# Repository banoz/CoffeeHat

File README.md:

# CoffeeHat

Basic espresso machine controls on Arduino Nano extension board.

Supports 3-Way valve control, PSM control for a vibe pump based on zero-crossing detector, Qwiic I2C connector for various peripherals (e.g. displays, thermal sensors), full header breakout for Nano pins.

# DISCLAIMER

This project is provided AS-IS, use at your sole discretion and your own risk. Parts of this project can work under dangerous voltages and require special care. Please don't do anything you're not sure about. The maintainer(s) can not be held liable for any suffer or loss or harm or anything else.

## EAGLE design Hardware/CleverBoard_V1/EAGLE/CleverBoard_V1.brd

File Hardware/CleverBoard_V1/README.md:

# Clever board

ESP32-C6 based controller board v1 - WIP

```
J10, J11 - AC input
J12 - pump
J13 - 3-way valve

J1 - UART0 (IO16/IO17)
J2 - I2C (IO6/IO7)
J3 - IO8, IO9
J5 - IO3
J6 - Pressure sensor (IO2, 10K/20K voltage divider)
J7 - Brew (IO22) / Steam (IO23) switch
J8 - IO19, IO20, IO21
J9 - 5V SSR control (IO10 -> SSR1, IO11 -> SSR2)

AC zero-cross sense on IO0
Pump control on IO18
3-Way valve control on IO15

I2C port on IO7(I2C1_SCL)/IO6(I2C1_SDA)
```

Top|Bottom
---|---
|

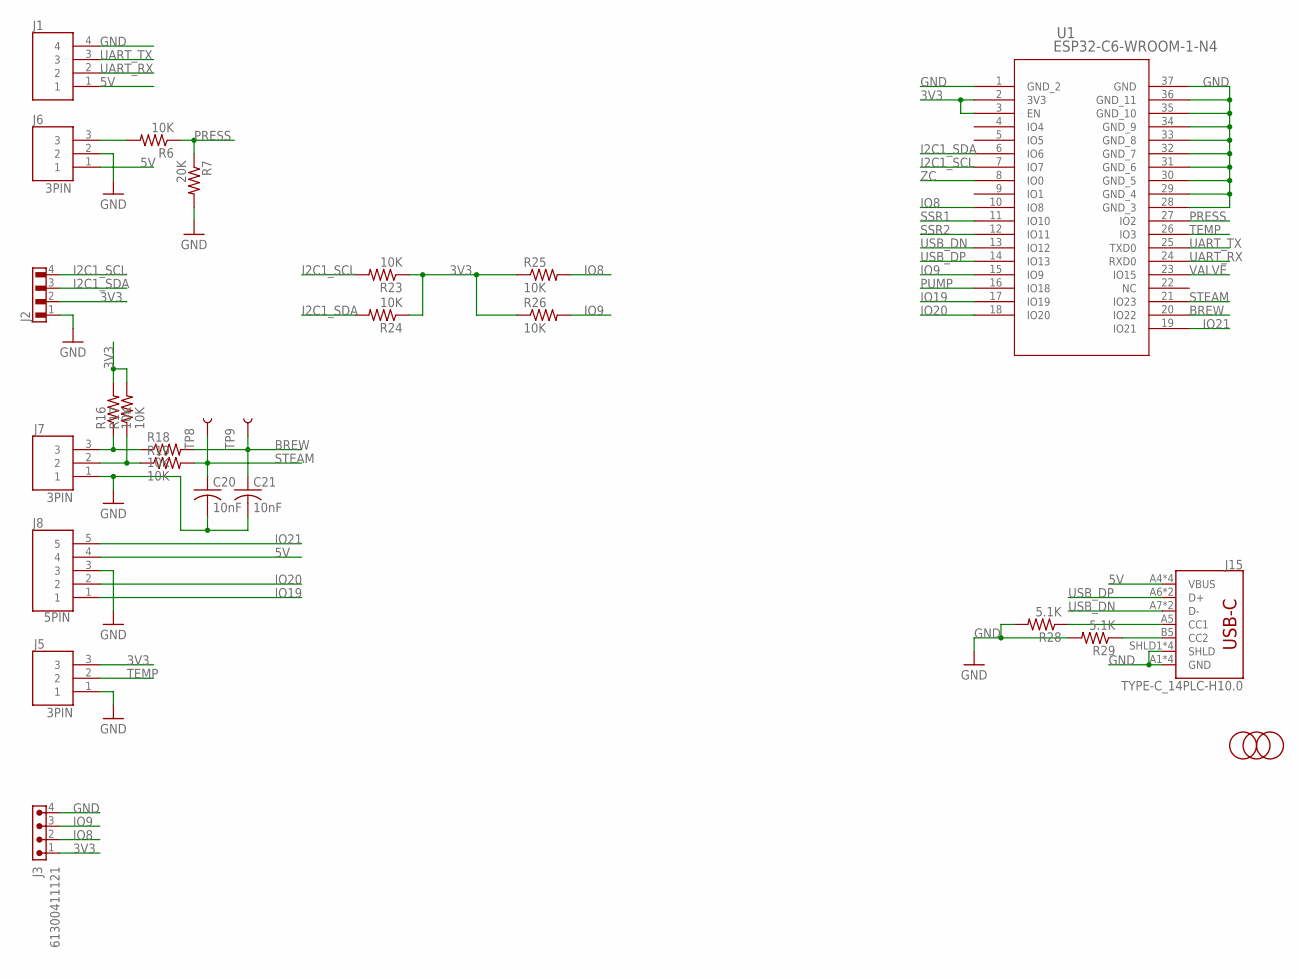
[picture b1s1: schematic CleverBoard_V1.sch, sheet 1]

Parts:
C20, C21: 10nF; C0603; LCSC C100042
J1: 4PIN; B4B-PH-K-S; LCSC C131334
J2: 665104131822; LCSC C160390
J3: 61300411121; LCSC C2691448
J5, J6, J7: 3PIN; B3B-PH-K-S; LCSC C131339
J8: 5PIN; B5B-PH-K-S; LCSC C157993
J15: TYPE-C_14PLC-H10.0; LCSC C3151746
MARK1, MARK2, MARK5: FIDUCIAL; FIDUCIAL_1MM
R6, R16, R17, R18, R19, R23, R24, R25, R26: 10K; R0603; LCSC C98220
R7: 20K; R0603; LCSC C105575
R28, R29: 5.1K; R0603; LCSC C105580
TP8, TP9: TEST-POINT3; PAD.03X.03
U1: ESP32-C6-WROOM-1-N4; MOD28_ESP32-C6-WROOM-1_EXP; LCSC C5366877

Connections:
3V3: J2.2, J3.1, J5.3, R16.2, R17.2, R23.1, R24.1, R25.1, R26.1, U1.2 (3V3), U1.3 (EN); also elsewhere on the board
5V: J1.1, J6.1, J8.4, J15.A4 (VBUS), J15.A9 (VBUS), J15.B4 (VBUS), J15.B9 (VBUS); also elsewhere on the board
BREW: C21.1, R18.2, TP9.1, U1.20 (IO22)
CC1: J15.A5 (CC1), R28.1
CC2: J15.B5 (CC2), R29.1
GND: C20.2, C21.2, J1.4, J2.1, J3.4, J5.1, J6.2, J7.1, J8.3, J15.A1 (GND), J15.A12 (GND), J15.B1 (GND), J15.B12 (GND), J15.SHLD1 (SHLD), J15.SHLD2 (SHLD), J15.SHLD3 (SHLD), J15.SHLD4 (SHLD), R7.2, R28.2, R29.2, U1.1 (GND_2), U1.28 (GND_3), U1.29 (GND_4), U1.30 (GND_5), U1.31 (GND_6), U1.32 (GND_7), U1.33 (GND_8), U1.34 (GND_9), U1.35 (GND_10), U1.36 (GND_11), U1.37 (GND); also elsewhere on the board
I2C1_SCL: J2.4, R23.2, U1.7 (IO7)
I2C1_SDA: J2.3, R24.2, U1.6 (IO6)
IO8: J3.2, R25.2, U1.10 (IO8)
IO9: J3.3, R26.2, U1.15 (IO9)
IO19: J8.1, U1.17 (IO19)
IO20: J8.2, U1.18 (IO20)
IO21: J8.5, U1.19 (IO21)
unnamed: J7.3, R16.1, R18.1
unnamed: J7.2, R17.1, R19.1
unnamed: J6.3, R6.2
PRESS: R6.1, R7.1, U1.27 (IO2)
PUMP: U1.16 (IO18); also elsewhere on the board
SSR1: U1.11 (IO10); also elsewhere on the board
SSR2: U1.12 (IO11); also elsewhere on the board
STEAM: C20.1, R19.2, TP8.1, U1.21 (IO23)
TEMP: J5.2, U1.26 (IO3)
UART_RX: J1.2, U1.24 (RXD0)
UART_TX: J1.3, U1.25 (TXD0)
USB_DN: J15.A7 (D-), J15.B7 (D-), U1.13 (IO12)
USB_DP: J15.A6 (D+), J15.B6 (D+), U1.14 (IO13)
VALVE: U1.23 (IO15); also elsewhere on the board
ZC: U1.8 (IO0); also elsewhere on the board

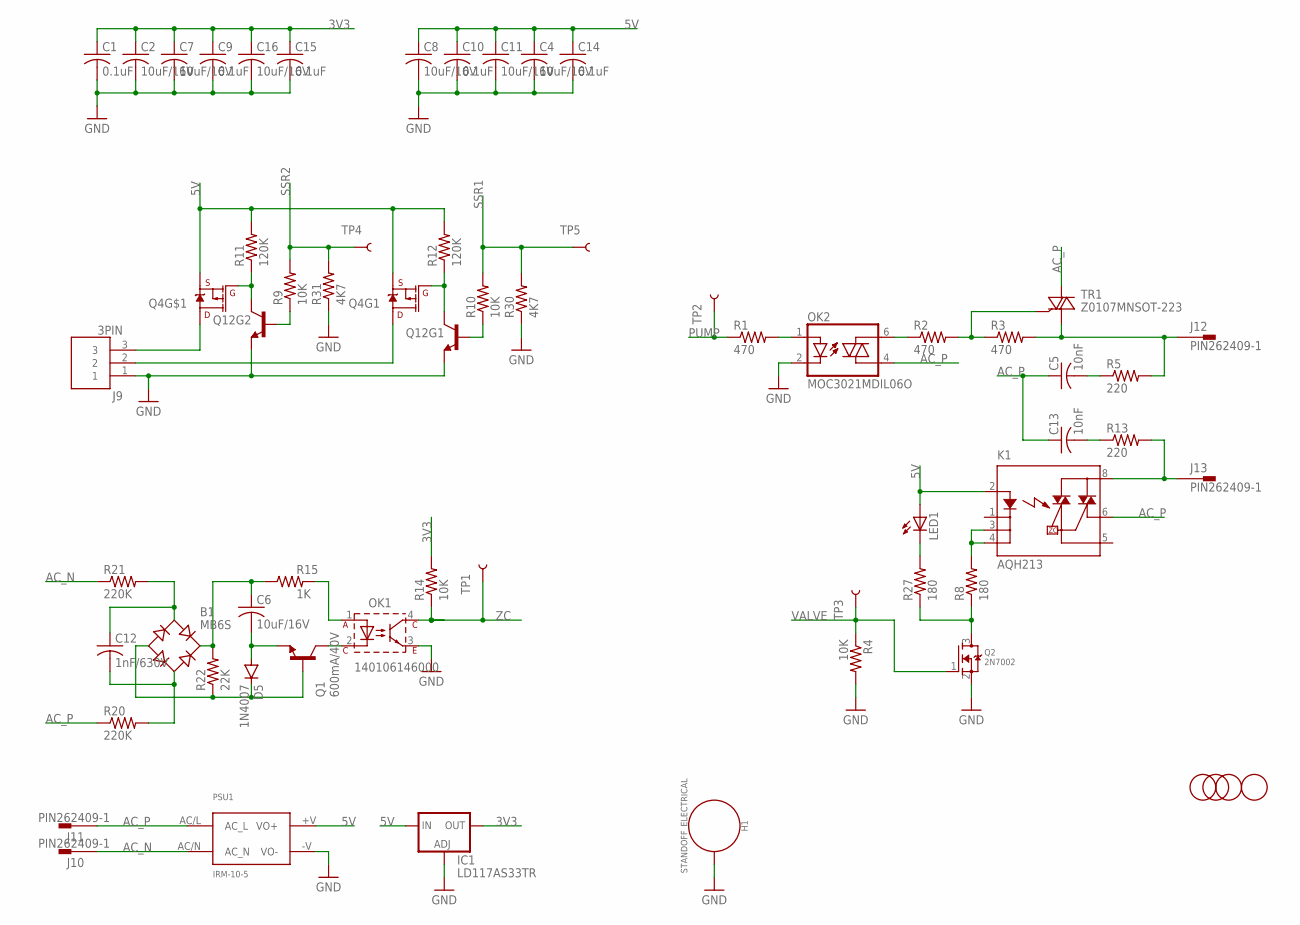
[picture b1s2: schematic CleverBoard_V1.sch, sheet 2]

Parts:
B1: MB6S; SOIC-4; LCSC C2487
C1, C9, C10, C14, C15: 0.1uF; C0603; LCSC C1591
C2, C4, C6, C7, C8, C11, C16: 10uF/16V; C0603; LCSC C86275
C5, C13: 10nF; C1206; LCSC C107192
C12: 1nF/630V; C0805; LCSC C501242
D5: 1N4007; DO214AC; LCSC C727081
H1: STANDOFF_ELECTRICAL; STANDOFF-ELECTRICAL
IC1: LD117AS33TR; SOT223; LCSC C26537
J9: 3PIN; B3B-PH-K-S; LCSC C131339
J10, J11, J12, J13: PIN262409-1; 62409-1; LCSC C86495
K1: AQH213; DIL07; LCSC C719560
LED1: LEDCHIP-LED0603; CHIP-LED0603; LCSC C2286
MARK4, MARK6, MARK7, MARK8: FIDUCIAL; FIDUCIAL_1MM
OK1: 140106146000; WL-OCPT_LSOP4; LCSC C141610
OK2: MOC3021MDIL06O; DIL06O; LCSC C5242
PSU1: IRM-10-5; IRM-10; LCSC C2857903
Q1: 600mA/40V; SOT23-3; LCSC C82460
Q2: 2N7002; SOT23-R; LCSC C65189
Q4: MOSFET_PCH_DUAL-DMP2240UDM; SOT26; LCSC C397948
Q12: TRANS_NPN_DUAL-MBT3904DW1T1; SC70-6; LCSC C896759
R1, R2, R3: 470; R0603; LCSC C114669
R4, R9, R10, R14: 10K; R0603; LCSC C98220
R5, R13: 220; R2512; LCSC C877859
R8, R27: 180; R0603; LCSC C137786
R11, R12: 120K; R0603; LCSC C114607
R15: 1K; R0603; LCSC C22548
R20, R21: 220K; R1206; LCSC C130275
R22: 22K; R0603; LCSC C114065
R30, R31: 4K7; R0603; LCSC C99782
TP1, TP2, TP3, TP4, TP5: TEST-POINT3; PAD.03X.03
TR1: Z0107MNSOT-223; SOT223; LCSC C71218

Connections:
3V3: C1.1, C2.1, C7.1, C9.1, C15.1, C16.1, IC1.4 (OUT), R14.2; also elsewhere on the board
3WAY: J13.A1, J13.A2, K1.8 (DS1), R13.2
5V: C4.1, C8.1, C10.1, C11.1, C14.1, IC1.3 (IN), K1.2 (A), LED1.A, PSU1.+V (VO+), Q4.S1 (S), Q4.S2 (S), R11.2, R12.2; also elsewhere on the board
AC_N: J10.A1, J10.A2, PSU1.AC/N (AC_N), R21.1
AC_P: C5.1, C13.1, J11.A1, J11.A2, K1.6 (DS3), OK2.4 (A1), PSU1.AC/L (AC_L), R20.1, TR1.2 (A2), TR1.4 (A2)
GND: C1.2, C2.2, C4.2, C7.2, C8.2, C9.2, C10.2, C11.2, C14.2, C15.2, C16.2, H1.P1, IC1.1 (ADJ), J9.1, OK1.3, OK2.2 (C), PSU1.-V (VO-), Q2.2 (S), Q12.1 (E), Q12.4 (E), R4.2, R30.1, R31.1; also elsewhere on the board
unnamed: B1.-, D5.C, Q1.1 (B), R22.1
unnamed: LED1.C, R27.2
unnamed: OK2.6 (A2), R2.1
unnamed: OK1.2, Q1.3 (C)
unnamed: R2.2, R3.1, TR1.3 (G)
unnamed: Q2.3 (D), R8.1, R27.1
unnamed: K1.3 (K1), K1.4 (K2), R8.2
unnamed: C13.2, R13.1
unnamed: C5.2, R5.1
unnamed: B1.~1 (AC1), C12.2, R20.2
unnamed: B1.~2 (AC2), C12.1, R21.2
unnamed: OK2.1 (A), R1.2
unnamed: C6.2, D5.A, Q1.2 (E)
unnamed: OK1.1, R15.2
unnamed: B1.+, C6.1, R15.1, R22.2
unnamed: Q12.2 (B), R9.1
unnamed: Q4.G1 (G), Q12.3 (C), R12.1
unnamed: Q4.G2 (G), Q12.6 (C), R11.1
unnamed: Q12.5 (B), R10.1
PUMP: R1.1, TP2.1; also elsewhere on the board
PUMP_P: J12.A1, J12.A2, R3.2, R5.2, TR1.1 (A1)
R1: J9.2, Q4.D1 (D)
R2: J9.3, Q4.D2 (D)
SSR1: R10.2, R30.2, TP5.1; also elsewhere on the board
SSR2: R9.2, R31.2, TP4.1; also elsewhere on the board
VALVE: Q2.1 (G), R4.1, TP3.1; also elsewhere on the board
ZC: OK1.4, R14.1, TP1.1; also elsewhere on the board

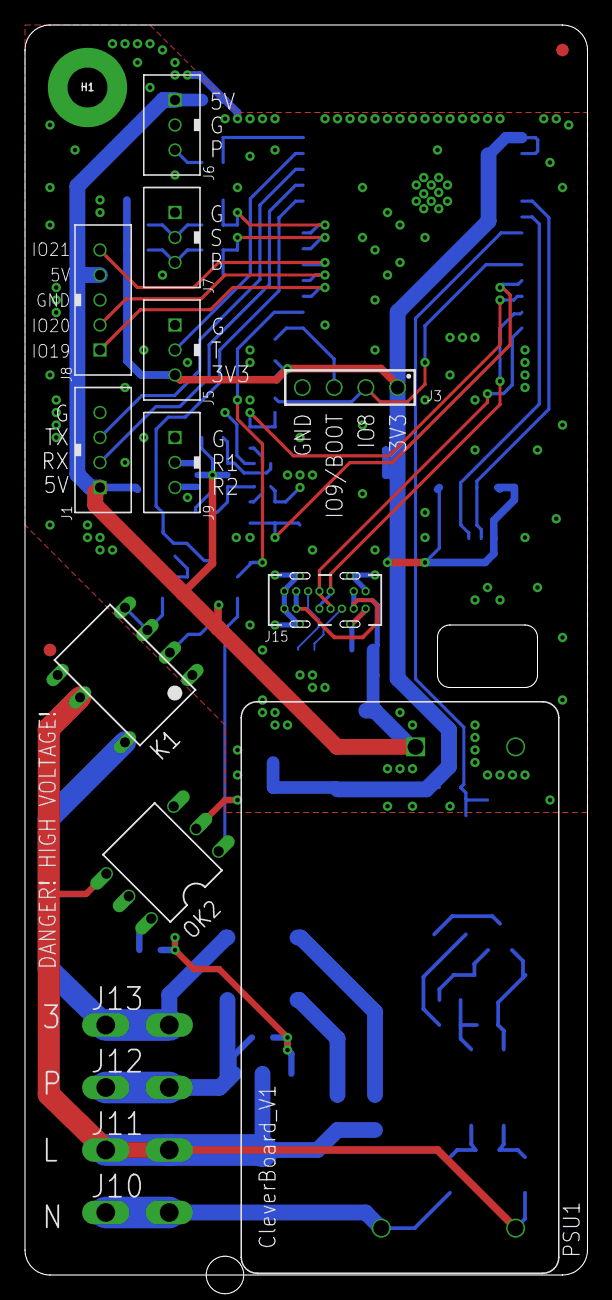
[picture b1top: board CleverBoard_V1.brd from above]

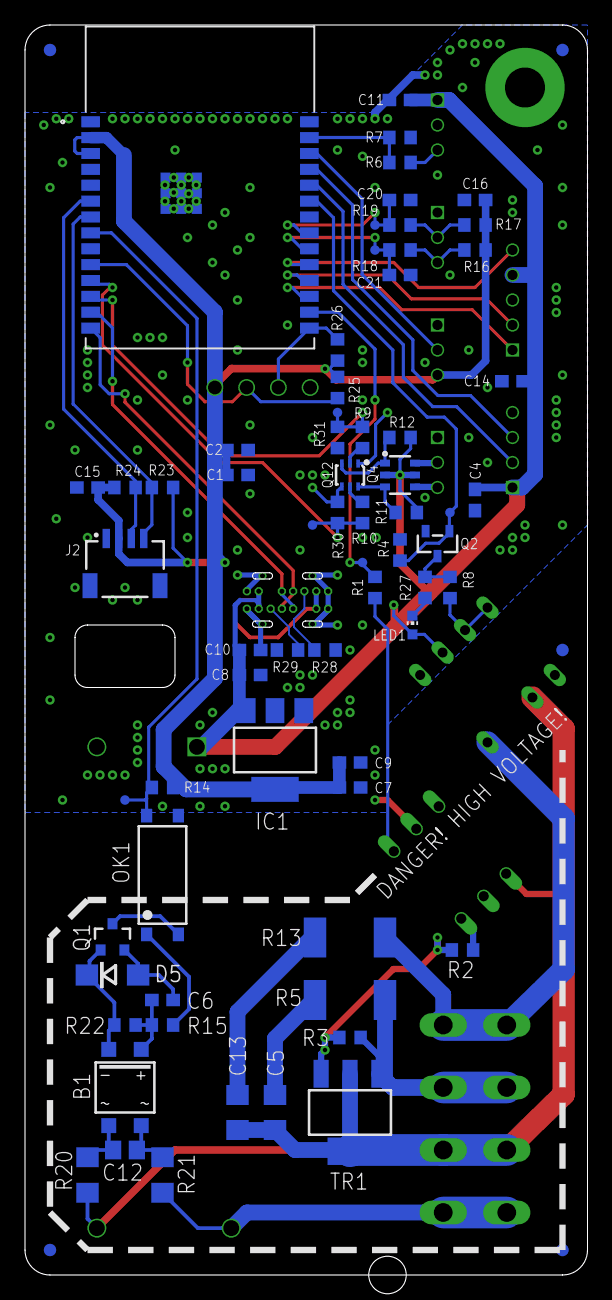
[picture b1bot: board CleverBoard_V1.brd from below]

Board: 2 copper layers, 45.0 x 100.0 mm, 90 parts (72 on the bottom side), 53 nets.

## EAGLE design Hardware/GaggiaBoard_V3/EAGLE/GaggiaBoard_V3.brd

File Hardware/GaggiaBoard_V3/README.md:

# Gaggiuino board

Gaggiuino hardware controller board v3 - WIP

[3D model](https://github.com/banoz/banoz.github.io/blob/main/repository/stl/GaggiaBoard_V3.stl)

```
J10, J11 - AC input
J12 - pump
J13 - 3-way valve

J1 - UART2 (PA2/PA3)
J2 - I2C
J4 - thermocouple
J6 - Pressure sensor (ADS101X/ADS111X on I2C1)
J7 - Brew (PC14) / Steam (PC15) switch
J8 - Scales (PB0 -> CLK, PB8 -> D1, PB9 -> D2)
J9 - 5V SSR control (PA15 -> SSR1, PA8 -> SSR2)

AC zero-cross sense on PA0
Pump control on PA1
3-Way valve control on PC13

SPI1 is used by thermocouple amplifier on PA5(SPI1_SCK)/PB4(SPI1_MISO), and CS on PA6

I2C port on PB6(I2C1_SCL)/PB7(I2C1_SDA)

J27 - USART1 (PA9/10) with NRST and BOOT1
```

Top|Bottom
---|---
|

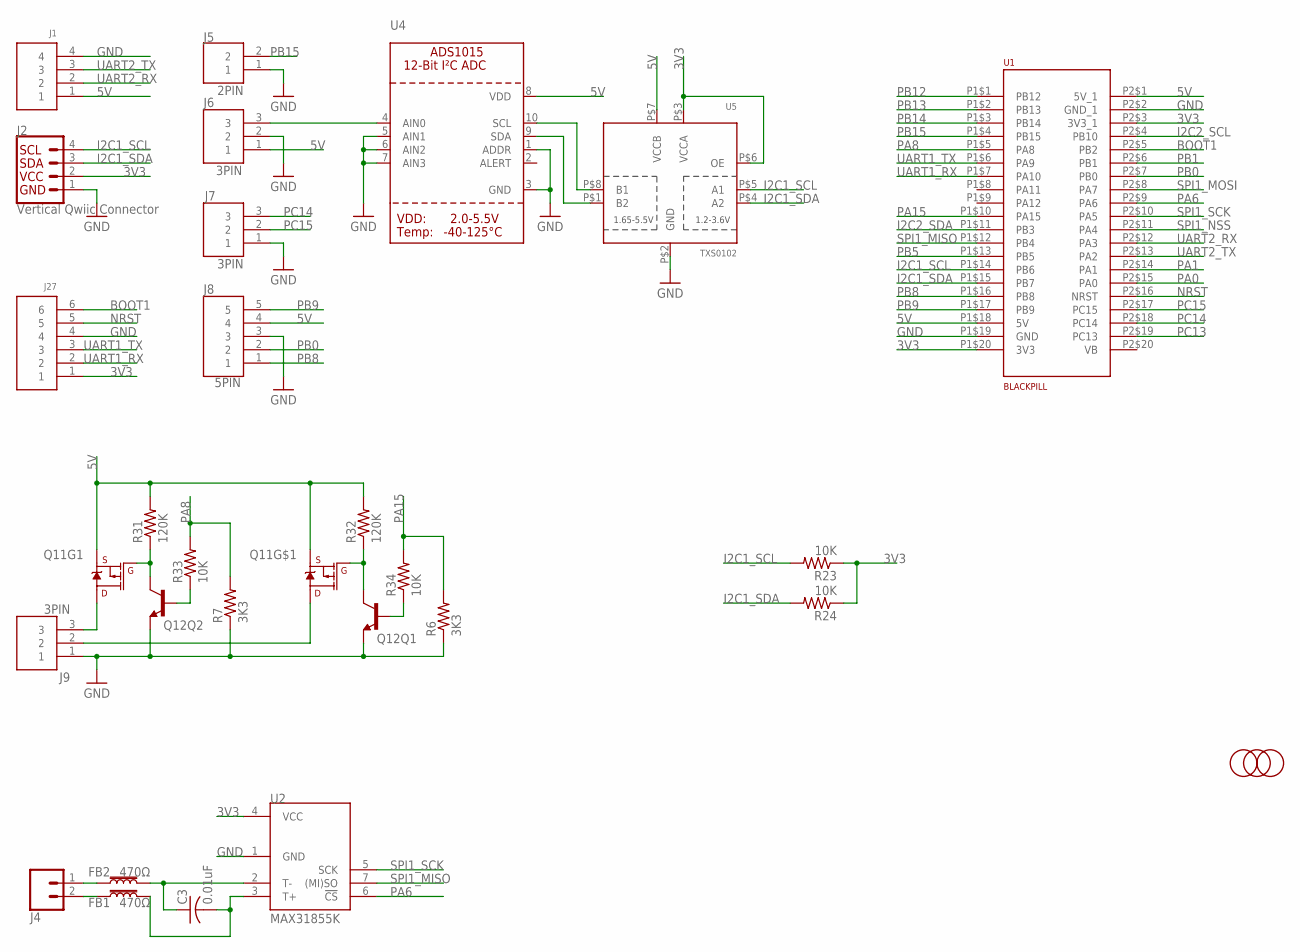
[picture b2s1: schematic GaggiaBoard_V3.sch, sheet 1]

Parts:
C3: 0.01uF; C0603; LCSC C100042
FB1, FB2: 470Ω; 0603; LCSC C883591
J1: 4PIN; B4B-PH-K-S; LCSC C131334
J2: Vertical Qwiic Connector; JST04_1MM_VERT; LCSC C160390
J4: CONN_023.5MM-NO_SILK; SCREWTERMINAL-3.5MM-2-NS; LCSC C474892
J5: 2PIN; B2B-PH-K-S; LCSC C131337
J6, J7, J9: 3PIN; B3B-PH-K-S; LCSC C131339
J8: 5PIN; B5B-PH-K-S; LCSC C157993
J27: 6PIN; B6B-PH-K-S; LCSC C131342
MARK1, MARK2, MARK5: FIDUCIAL; FIDUCIAL_1MM
Q11: MOSFET_PCH_DUAL-DMP2240UDM; SOT26; LCSC C397948
Q12: TRANS_NPN_DUAL-MBT3904DW1T1; SC70-6; LCSC C896759
R6, R7: 3K3; R0603; LCSC C114432
R23, R24, R33, R34: 10K; R0603; LCSC C98220
R31, R32: 120K; R0603; LCSC C114607
U1: BLACKPILL
U2: MAX31855K; SO08; LCSC C52028
U4: ADC_ADS1015; MSOP10; LCSC C193969
U5: TXS0102; VFSOP-8; LCSC C53434

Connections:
3V3: J2.2, J27.1, R23.1, R24.1, U1.P1$20 (3V3), U1.P2$3 (3V3_1), U2.4 (VCC), U5.P$3 (VCCA), U5.P$6 (OE); also elsewhere on the board
5V: J1.1, J6.1, J8.4, Q11.S1 (S), Q11.S2 (S), R31.2, R32.2, U1.P1$18 (5V), U1.P2$1 (5V_1), U4.8 (VDD), U5.P$7 (VCCB); also elsewhere on the board
BOOT1: J27.6, U1.P2$5 (PB2)
GND: J1.4, J2.1, J5.1, J6.2, J7.1, J8.3, J9.1, J27.4, Q12.1 (E), Q12.4 (E), R6.1, R7.1, U1.P1$19 (GND), U1.P2$2 (GND_1), U2.1 (GND), U4.1 (ADDR), U4.3 (GND), U4.5 (AIN1), U4.6 (AIN2), U4.7 (AIN3), U5.P$2 (GND); also elsewhere on the board
I2C1_SCL: J2.4, R23.2, U1.P1$14 (PB6), U5.P$5 (A1)
I2C1_SDA: J2.3, R24.2, U1.P1$15 (PB7), U5.P$4 (A2)
I2C2_SCL: U1.P2$4 (PB10)
I2C2_SDA: U1.P1$11 (PB3)
unnamed: FB2.1, J4.1
unnamed: FB1.1, J4.2
unnamed: C3.1, FB2.2, U2.2 (T-)
unnamed: J9.3, Q11.D1 (D)
unnamed: J9.2, Q11.D2 (D)
unnamed: U4.10 (SCL), U5.P$8 (B1)
unnamed: C3.2, FB1.2, U2.3 (T+)
unnamed: U4.9 (SDA), U5.P$1 (B2)
unnamed: Q12.2 (B), R33.1
unnamed: Q11.G2 (G), Q12.3 (C), R32.1
unnamed: Q11.G1 (G), Q12.6 (C), R31.1
unnamed: Q12.5 (B), R34.1
NRST: J27.5, U1.P2$16 (NRST)
PA0: U1.P2$15 (PA0); also elsewhere on the board
PA1: U1.P2$14 (PA1); also elsewhere on the board
PA6: U1.P2$9 (PA6), U2.6 (!CS)
PA8: R7.2, R33.2, U1.P1$5 (PA8)
PA15: R6.2, R34.2, U1.P1$10 (PA15)
PB0: J8.2, U1.P2$7 (PB0)
PB1: U1.P2$6 (PB1)
PB5: U1.P1$13 (PB5)
PB8: J8.1, U1.P1$16 (PB8)
PB9: J8.5, U1.P1$17 (PB9)
PB12: U1.P1$1 (PB12)
PB13: U1.P1$2 (PB13)
PB14: U1.P1$3 (PB14)
PB15: J5.2, U1.P1$4 (PB15)
PC13: U1.P2$19 (PC13); also elsewhere on the board
PC14: J7.3, U1.P2$18 (PC14)
PC15: J7.2, U1.P2$17 (PC15)
PRESSURE: J6.3, U4.4 (AIN0)
SPI1_MISO: U1.P1$12 (PB4), U2.7 ((MI)SO)
SPI1_MOSI: U1.P2$8 (PA7)
SPI1_NSS: U1.P2$11 (PA4)
SPI1_SCK: U1.P2$10 (PA5), U2.5 (SCK)
UART1_RX: J27.2, U1.P1$7 (PA10)
UART1_TX: J27.3, U1.P1$6 (PA9)
UART2_RX: J1.2, U1.P2$12 (PA3)
UART2_TX: J1.3, U1.P2$13 (PA2)

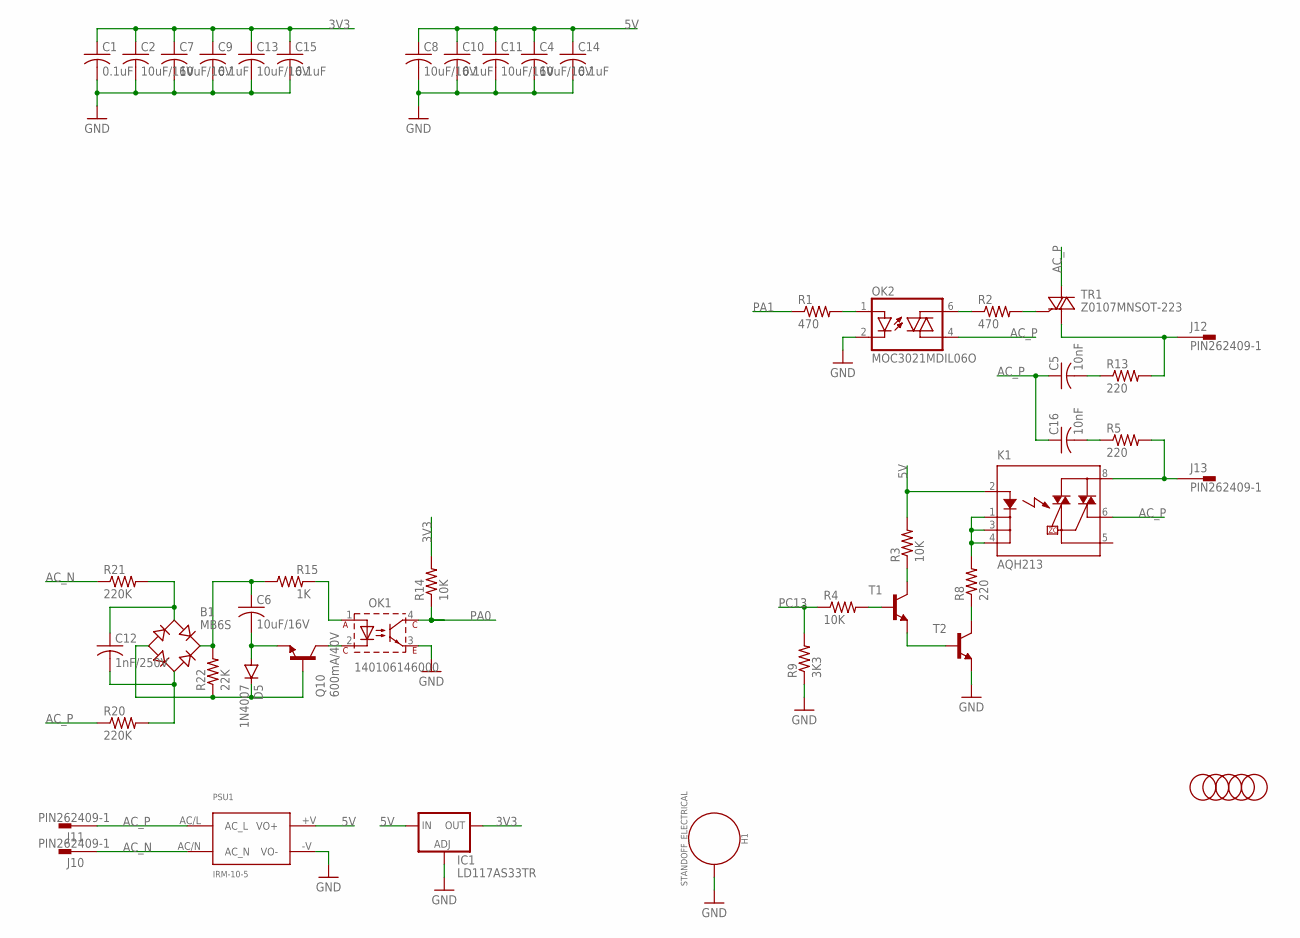
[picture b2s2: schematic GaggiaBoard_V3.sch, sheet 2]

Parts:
B1: MB6S; SOIC-4; LCSC C2487
C1, C9, C10, C14, C15: 0.1uF; C0603; LCSC C1591
C2, C4, C6, C7, C8, C11, C13: 10uF/16V; C0603; LCSC C86275
C5, C16: 10nF; C1206; LCSC C107192
C12: 1nF/250V; C0603; LCSC C277510
D5: 1N4007; DO214AC; LCSC C727081
H1: STANDOFF_ELECTRICAL; STANDOFF-ELECTRICAL
IC1: LD117AS33TR; SOT223; LCSC C26537
J10, J11, J12, J13: PIN262409-1; 62409-1; LCSC C86495
K1: AQH213; DIL07; LCSC C719560
MARK3, MARK4, MARK6, MARK7, MARK8: FIDUCIAL; FIDUCIAL_1MM
OK1: 140106146000; WL-OCPT_LSOP4; LCSC C141610
OK2: MOC3021MDIL06O; DIL06O; LCSC C5242
PSU1: IRM-10-5; IRM-10; LCSC C2857903
Q10: 600mA/40V; SOT23-3; LCSC C82460
R1, R2: 470; R0603; LCSC C114669
R3, R4, R14: 10K; R0603; LCSC C98220
R5, R13: 220; R2512; LCSC C877859
R8: 220; R0603; LCSC C107696
R9: 3K3; R0603; LCSC C114432
R15: 1K; R0603; LCSC C22548
R20, R21: 220K; R1206; LCSC C130275
R22: 22K; R0603; LCSC C114065
T1, T2: MMBT2222ALT1-NPN-SOT23-BEC; SOT23-BEC; LCSC C82460
TR1: Z0107MNSOT-223; SOT223; LCSC C71218

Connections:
3V3: C1.1, C2.1, C7.1, C9.1, C13.1, C15.1, IC1.4 (OUT), R14.2; also elsewhere on the board
3WAY: J13.A1, J13.A2, K1.8 (DS1), R5.2
5V: C4.1, C8.1, C10.1, C11.1, C14.1, IC1.3 (IN), K1.2 (A), PSU1.+V (VO+), R3.2; also elsewhere on the board
AC_N: J10.A1, J10.A2, PSU1.AC/N (AC_N), R21.1
AC_P: C5.1, C16.1, J11.A1, J11.A2, K1.6 (DS3), OK2.4 (A1), PSU1.AC/L (AC_L), R20.1, TR1.2 (A2), TR1.4 (A2)
GND: C1.2, C2.2, C4.2, C7.2, C8.2, C9.2, C10.2, C11.2, C13.2, C14.2, C15.2, H1.P1, IC1.1 (ADJ), OK1.3, OK2.2 (C), PSU1.-V (VO-), R9.1, T2.E; also elsewhere on the board
unnamed: R3.1, T1.C
unnamed: B1.-, D5.C, Q10.1 (B), R22.1
unnamed: OK1.2, Q10.3 (C)
unnamed: OK2.6 (A2), R2.1
unnamed: R2.2, TR1.3 (G)
unnamed: R8.1, T2.C
unnamed: T1.E, T2.B
unnamed: K1.1 (K), K1.3 (K1), K1.4 (K2), R8.2
unnamed: R4.2, T1.B
unnamed: C16.2, R5.1
unnamed: C5.2, R13.1
unnamed: B1.~1 (AC1), C12.2, R20.2
unnamed: B1.~2 (AC2), C12.1, R21.2
unnamed: OK2.1 (A), R1.2
unnamed: C6.2, D5.A, Q10.2 (E)
unnamed: OK1.1, R15.2
unnamed: B1.+, C6.1, R15.1, R22.2
PA0: OK1.4, R14.1; also elsewhere on the board
PA1: R1.1; also elsewhere on the board
PC13: R4.1, R9.2; also elsewhere on the board
PUMP_P: J12.A1, J12.A2, R13.2, TR1.1 (A1)

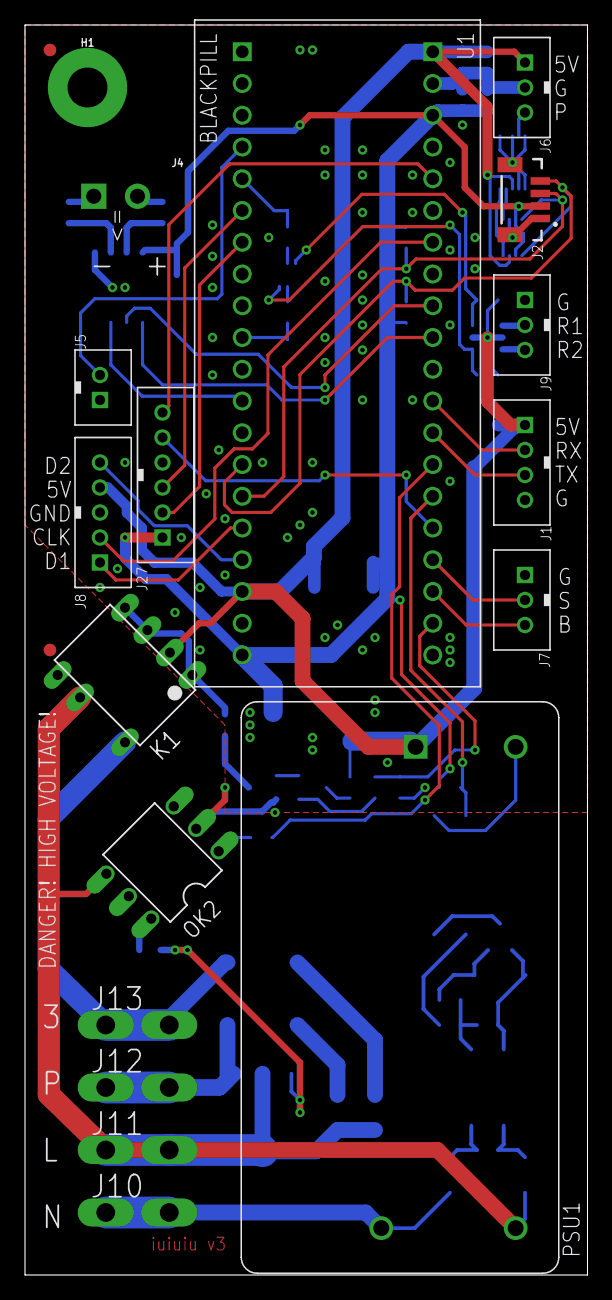
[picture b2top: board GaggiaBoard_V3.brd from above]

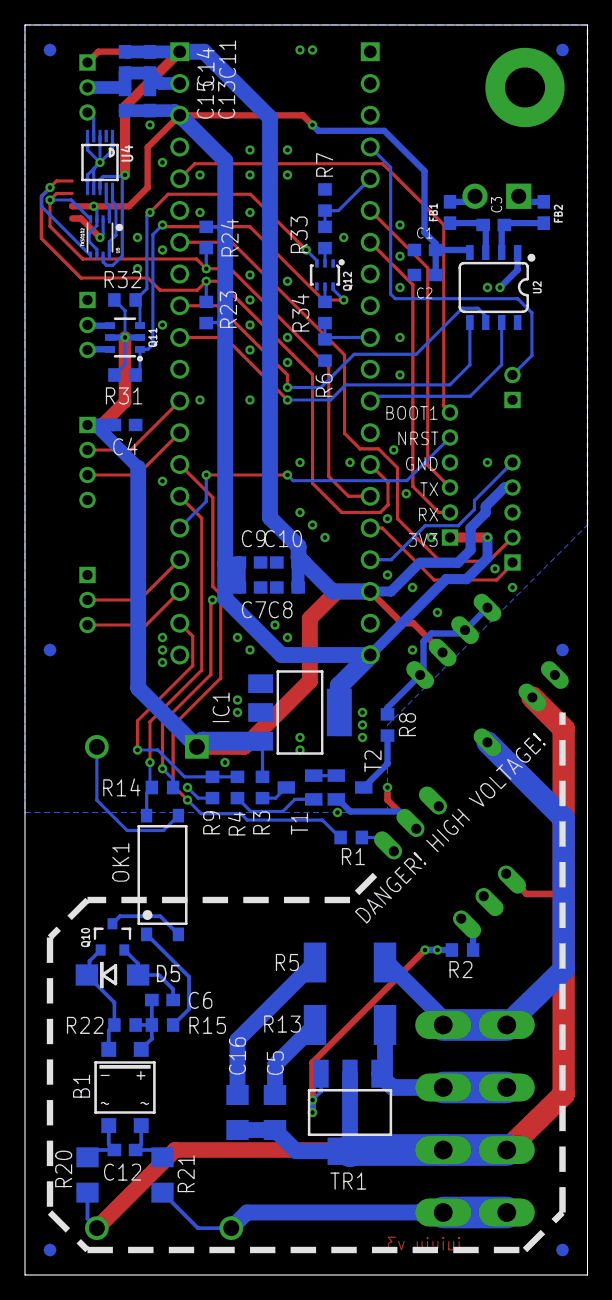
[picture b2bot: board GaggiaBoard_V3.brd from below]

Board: 2 copper layers, 45.0 x 100.0 mm, 78 parts (58 on the bottom side), 59 nets.

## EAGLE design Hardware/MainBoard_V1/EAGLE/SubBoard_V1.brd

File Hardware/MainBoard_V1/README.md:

# Generic espresso machine control board

Arduino Nano-based control board for an espresso maker.

**WIP**

SubBoard_V1 is an extension board to use on top of MainBoard_V1 for Gaggiuino.

Pin mapping:  

```
A0 - Pressure transducer

A1 - CLK  \
A2 - D1    -- dual HX711 scales
A3 - D2   /

A4 - I2C SDA
A5 - I2C SCL

D8 - Brew switch
D7 - Steam switch

D0 - NEXTION TX
D1 - NEXTION RX

D3 - AC zero-crossing

D4 - DO   \
D5 - CS    -- MAX31855
D6 - CLK  /

D9 - 3-way valve control
D10 - Pump TRIAC control
D11 - Boiler heater SSR control
```

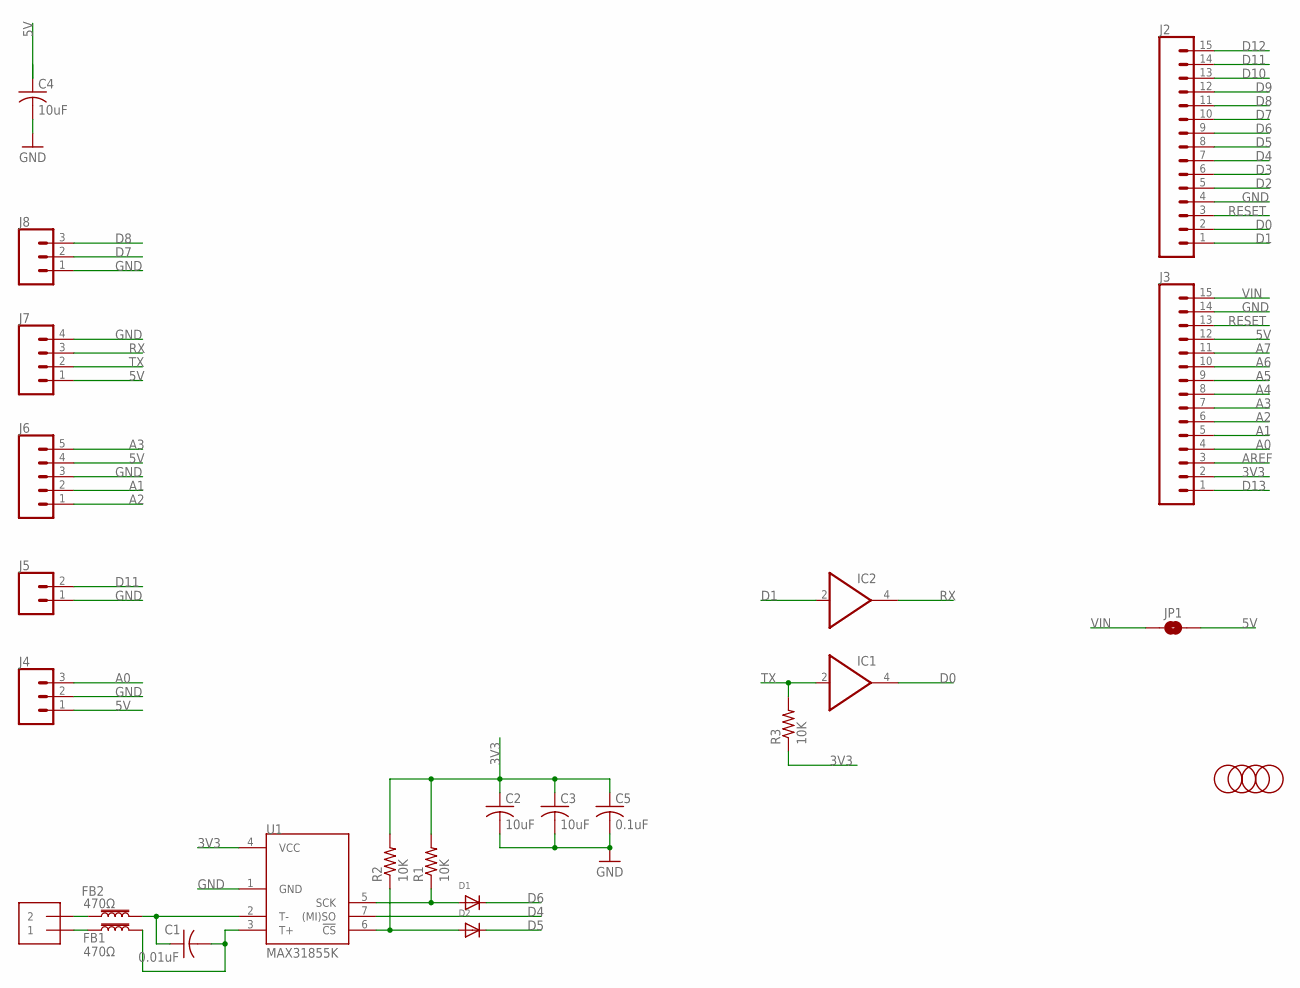
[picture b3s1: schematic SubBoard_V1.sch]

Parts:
C1: 0.01uF; C0603; LCSC C1589
C2, C3, C4: 10uF; C0603; LCSC C19702
C5: 0.1uF; C0603; LCSC C1591
D1, D2: DIODESOD-523; SOD-523; LCSC C232841
FB1, FB2: 470Ω; 0603; LCSC C883591
IC1, IC2: 74LVC1G07DBV; SOT23-5; LCSC C7829
J1: 1X2-3.5MM; LCSC C474892
J2, J3: CONN_15; 1X15; LCSC C2897378
J4, J8: CONN_03JST-PTH; JST-3-PTH; LCSC C157929
J5: CONN_02JST-PTH-2; JST-2-PTH; LCSC C173752
J6: CONN_05JST; JST-5-PTH; LCSC C157923
J7: CONN_04POLAR; MOLEX-1X4; LCSC C163037
JP1: JUMPER-SMT_2_NO_SILK; SMT-JUMPER_2_NO_SILK
R1, R2, R3: 10K; R0402; LCSC C60490
U1: MAX31855K; SO08; LCSC C52028
U$1, U$2, U$3, U$4: FIDUCIAL; FIDUCIAL_1MM

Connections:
3V3: C2.1, C3.1, C5.1, IC1.5 (VCC), IC2.5 (VCC), J3.2, R1.2, R2.2, R3.1, U1.4 (VCC)
5V: C4.1, J3.12, J4.1, J6.4, J7.1, JP1.2
A0: J3.4, J4.3
A1: J3.5, J6.2
A2: J3.6, J6.1
A3: J3.7, J6.5
A4: J3.8
A5: J3.9
A6: J3.10
A7: J3.11
AREF: J3.3
D0: IC1.4 (O), J2.2
D1: IC2.2 (I), J2.1
D2: J2.5
D3: J2.6
D4: J2.7, U1.7 ((MI)SO)
D5: D2.K (C), J2.8
D6: D1.K (C), J2.9
D7: J2.10, J8.2
D8: J2.11, J8.3
D9: J2.12
D10: J2.13
D11: J2.14, J5.2
D12: J2.15
D13: J3.1
GND: C2.2, C3.2, C4.2, C5.2, IC1.3 (GND), IC2.3 (GND), J2.4, J3.14, J4.2, J5.1, J6.3, J7.4, J8.1, U1.1 (GND)
unnamed: FB2.1, J1.2
unnamed: FB1.1, J1.1
unnamed: C1.1, FB2.2, U1.2 (T-)
unnamed: D1.A, R1.1, U1.5 (SCK)
unnamed: C1.2, FB1.2, U1.3 (T+)
unnamed: D2.A, R2.1, U1.6 (!CS)
RESET: J2.3, J3.13
RX: IC2.4 (O), J7.3
TX: IC1.2 (I), J7.2, R3.2
VIN: J3.15, JP1.1

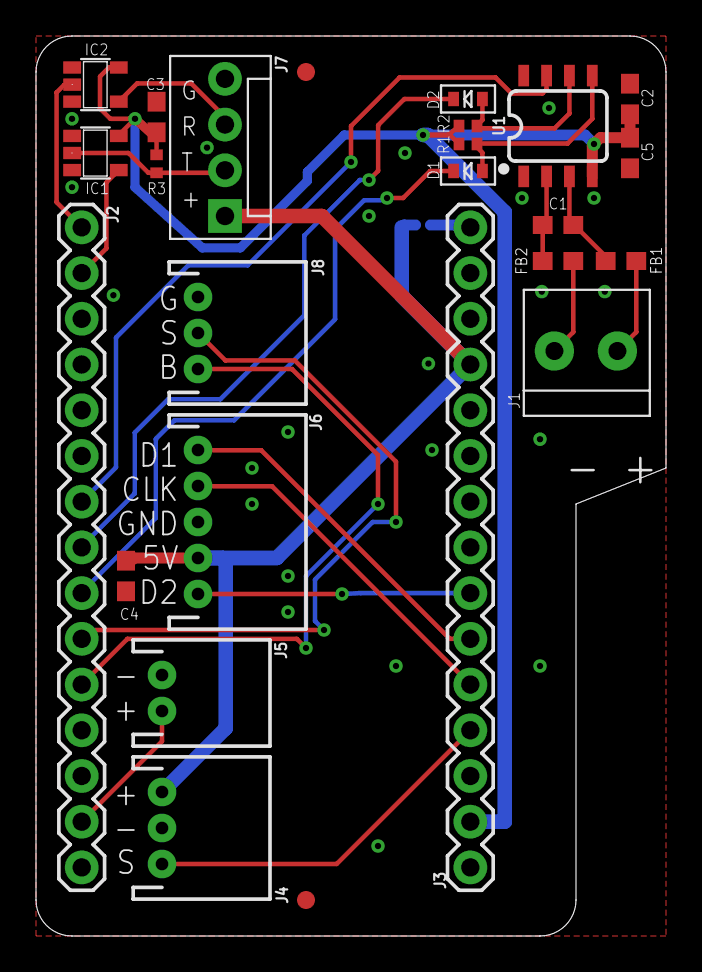
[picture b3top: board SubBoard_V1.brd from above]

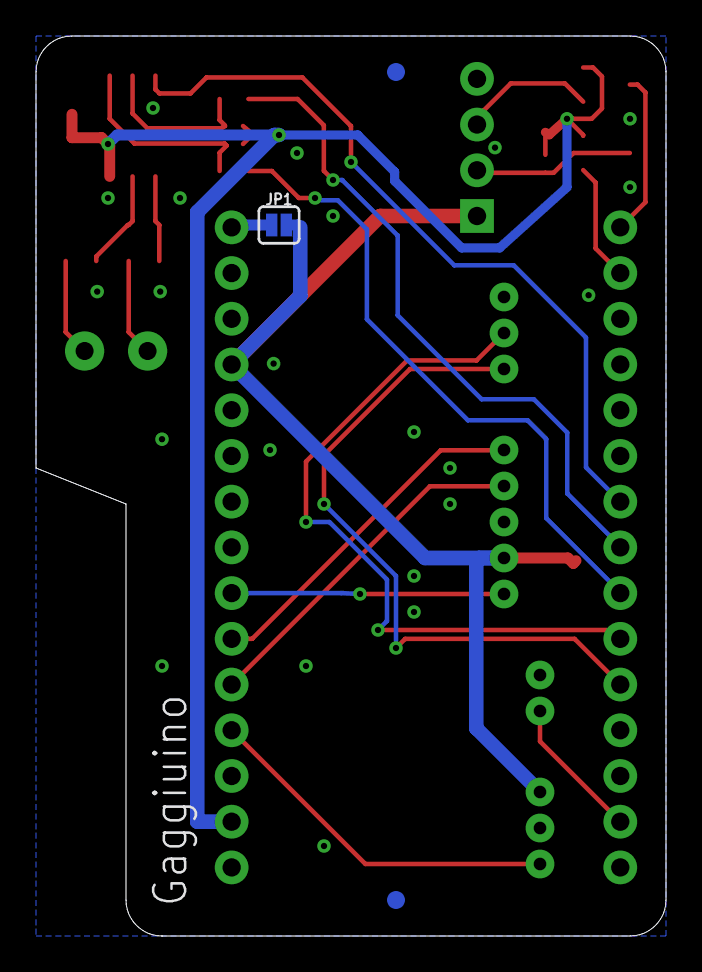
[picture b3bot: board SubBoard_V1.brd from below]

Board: 2 copper layers, 35.0 x 50.0 mm, 28 parts (3 on the bottom side), 25 nets.

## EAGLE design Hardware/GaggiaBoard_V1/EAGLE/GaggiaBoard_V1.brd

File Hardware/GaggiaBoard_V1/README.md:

# Gaggiuino board

Next-gen Gaggiuino hardware controller board - WIP
```
J22, J23 - AC input
J10, J11 - 3-way valve
J12, J13 - boiler 1 (J14, J15 - SSR for boiler 1)
J16, J17 - boiler 2 (J18, J19 - SSR for boiler 2)
J20, J21 - pump

J1 - UART6 (PA11/12)
J2, J3 - I2Cs
J4, J5 - thermocouples
J6 - Pressure sensor (ADS101X/ADS111X on I2C2)
J7 - Brew (PA1) / Steam (PA2) switch
J8 - Scales (PB0 -> CLK, PB1 -> D1, PB2 -> D2)
J9 - SSR control (PA6 -> SSR1, PA8 -> SSR2)

AC zero-cross sense on PA0
Buzzer on PB5
Pump control on PB8
Heater 1 relay on PC14
Heater 2 relay on PC13
3-Way valve control on PC15

SPI1 on PA4/5/7/PB4 pins is used by FLASH on board or MicroSD card

SPI2 is used for thermocouples on PB12(SPI2_NSS)/PB13(SPI2_SCK)/PB14(SPI2_MISO), and CS for second chip will be PB9(SPI2_NSS)

Two I2C ports on PB6(I2C1_SCL)/PB7(I2C1_SDA) and PB10(I2C2_SCL)/PB3(I2C2_SDA)

J27 - USART1 (PA9/10)
```

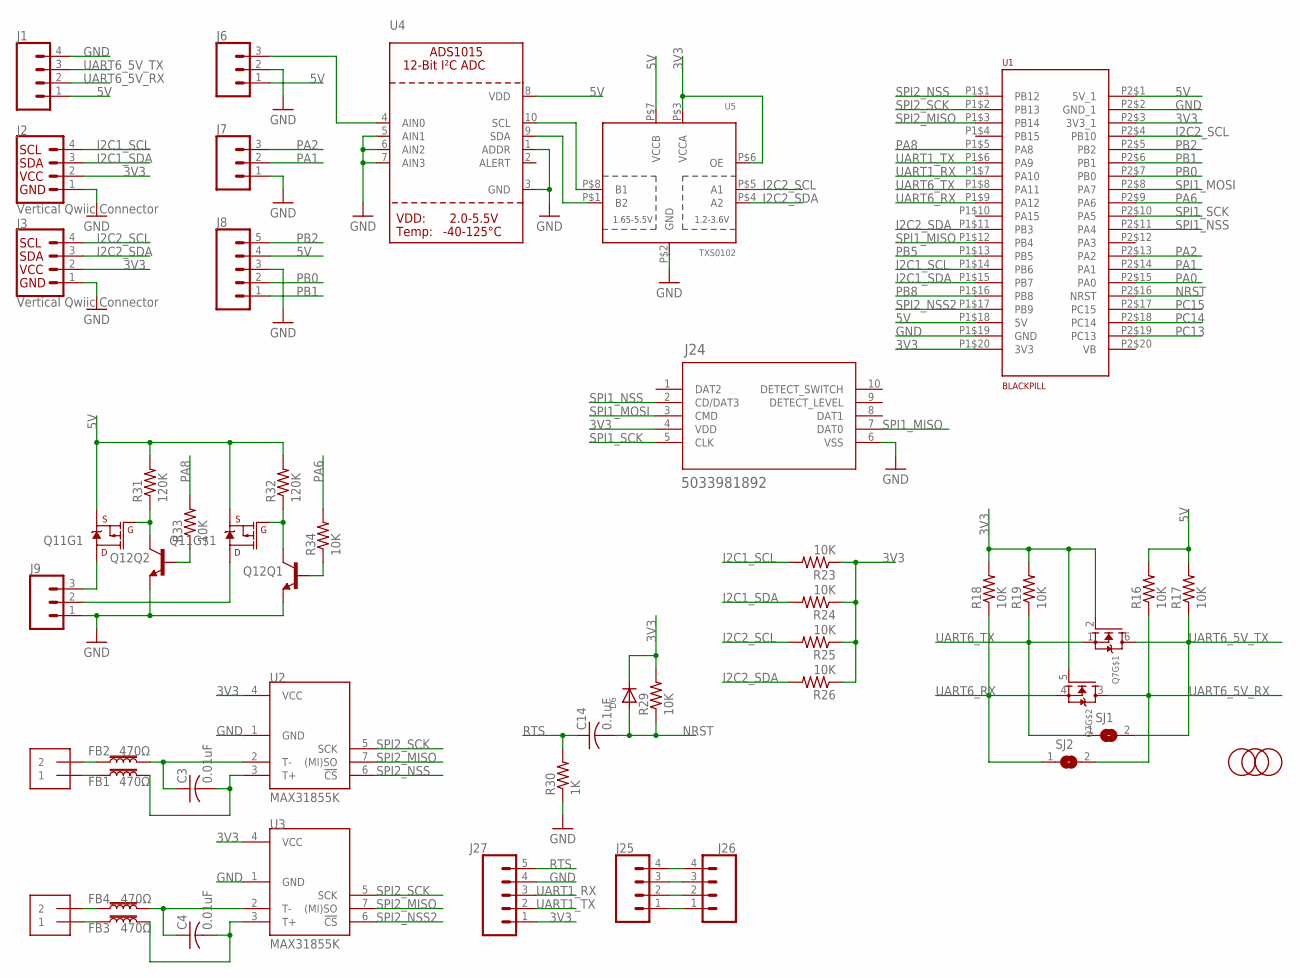
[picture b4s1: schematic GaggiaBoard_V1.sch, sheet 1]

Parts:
C3, C4: 0.01uF; C0603; LCSC C100042
C14: 0.1uF; C0603; LCSC C14663
D6: DIODESOD-123; SOD-123; LCSC C83528
FB1, FB2, FB3, FB4: 470Ω; 0603; LCSC C883591
J1: CONN_04POLAR; MOLEX-1X4; LCSC C144395
J2, J3: Vertical Qwiic Connector; JST04_1MM_VERT; LCSC C160390
J4, J5: 1X2-3.5MM; LCSC C474892
J6, J7, J9: CONN_03JST-PTH-VERT; JST-3-PTH-VERT; LCSC C131339
J8: CONN_05JST-VERT; JST-5-PTH-VERT; LCSC C157993
J24: 5033981892; 503398-1892_MOL; LCSC C428492
J25, J26: CONN_041X04_NO_SILK; 1X04_NO_SILK
J27: CONN_05NO_SILK; 1X05_NO_SILK
MARK1, MARK2, MARK5: FIDUCIAL; FIDUCIAL_1MM
Q7: MOSFET-N_DUAL; SOT363; LCSC C150488
Q11: MOSFET_PCH_DUAL-DMP2240UDM; SOT26; LCSC C397948
Q12: TRANS_NPN_DUAL-MBT3904DW1T1; SC70-6; LCSC C896759
R16, R17, R18, R19, R23, R24, R25, R26, R29, R33, R34: 10K; R0603; LCSC C98220
R30: 1K; R0603; LCSC C22548
R31, R32: 120K; R0603; LCSC C114607
SJ1, SJ2: SOLDERJUMPER; SOLDERJUMPER_ARROW_NOPASTE
U1: BLACKPILL
U2, U3: MAX31855K; SO08; LCSC C52028
U4: ADC_ADS1015; MSOP10; LCSC C193969
U5: TXS0102; VFSOP-8; LCSC C53434

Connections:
3V3: D6.C, J2.2, J3.2, J24.4 (VDD), J25.1, J26.1, J27.1, Q7.2 (G), Q7.5 (G), R18.2, R19.2, R23.1, R24.1, R25.1, R26.1, R29.2, U1.P1$20 (3V3), U1.P2$3 (3V3_1), U2.4 (VCC), U3.4 (VCC), U5.P$3 (VCCA), U5.P$6 (OE); also elsewhere on the board
5V: J1.1, J6.1, J8.4, Q11.S1 (S), Q11.S2 (S), R16.2, R17.2, R31.2, R32.2, U1.P1$18 (5V), U1.P2$1 (5V_1), U4.8 (VDD), U5.P$7 (VCCB); also elsewhere on the board
GND: J1.4, J2.1, J3.1, J6.2, J7.1, J8.3, J9.1, J24.6 (VSS), J25.4, J26.4, J27.4, Q12.1 (E), Q12.4 (E), R30.1, U1.P1$19 (GND), U1.P2$2 (GND_1), U2.1 (GND), U3.1 (GND), U4.1 (ADDR), U4.3 (GND), U4.5 (AIN1), U4.6 (AIN2), U4.7 (AIN3), U5.P$2 (GND); also elsewhere on the board
I2C1_SCL: J2.4, R23.2, U1.P1$14 (PB6)
I2C1_SDA: J2.3, R24.2, U1.P1$15 (PB7)
I2C2_SCL: J3.4, R25.2, U1.P2$4 (PB10), U5.P$5 (A1)
I2C2_SDA: J3.3, R26.2, U1.P1$11 (PB3), U5.P$4 (A2)
unnamed: FB2.1, J4.2
unnamed: FB1.1, J4.1
unnamed: C3.1, FB2.2, U2.2 (T-)
unnamed: FB4.1, J5.2
unnamed: U4.10 (SCL), U5.P$8 (B1)
unnamed: FB3.1, J5.1
unnamed: C4.1, FB4.2, U3.2 (T-)
unnamed: C3.2, FB1.2, U2.3 (T+)
unnamed: C4.2, FB3.2, U3.3 (T+)
unnamed: U4.9 (SDA), U5.P$1 (B2)
unnamed: J9.2, Q11.D2 (D)
unnamed: J9.3, Q11.D1 (D)
unnamed: Q12.2 (B), R33.1
unnamed: Q11.G2 (G), Q12.3 (C), R32.1
unnamed: Q11.G1 (G), Q12.6 (C), R31.1
unnamed: Q12.5 (B), R34.1
NRST: C14.2, D6.A, R29.1, U1.P2$16 (NRST)
PA0: U1.P2$15 (PA0); also elsewhere on the board
PA1: J7.2, U1.P2$14 (PA1)
PA2: J7.3, U1.P2$13 (PA2)
PA6: R34.2, U1.P2$9 (PA6)
PA8: R33.2, U1.P1$5 (PA8)
PB0: J8.2, U1.P2$7 (PB0)
PB1: J8.1, U1.P2$6 (PB1)
PB2: J8.5, U1.P2$5 (PB2)
PB5: U1.P1$13 (PB5); also elsewhere on the board
PB8: U1.P1$16 (PB8); also elsewhere on the board
PC13: U1.P2$19 (PC13); also elsewhere on the board
PC14: U1.P2$18 (PC14); also elsewhere on the board
PC15: U1.P2$17 (PC15); also elsewhere on the board
PRESSURE: J6.3, U4.4 (AIN0)
RTS: C14.1, J27.5, R30.2
SPI1_MISO: J24.7 (DAT0), U1.P1$12 (PB4)
SPI1_MOSI: J24.3 (CMD), U1.P2$8 (PA7)
SPI1_NSS: J24.2 (CD/DAT3), U1.P2$11 (PA4)
SPI1_SCK: J24.5 (CLK), U1.P2$10 (PA5)
SPI2_MISO: U1.P1$3 (PB14), U2.7 ((MI)SO), U3.7 ((MI)SO)
SPI2_NSS: U1.P1$1 (PB12), U2.6 (!CS)
SPI2_NSS2: U1.P1$17 (PB9), U3.6 (!CS)
SPI2_SCK: U1.P1$2 (PB13), U2.5 (SCK), U3.5 (SCK)
SWCLK: J25.3, J26.3
SWDIO: J25.2, J26.2
UART1_RX: J27.3, U1.P1$7 (PA10)
UART1_TX: J27.2, U1.P1$6 (PA9)
UART6_5V_RX: J1.2, Q7.3 (D), R16.1, SJ2.2
UART6_5V_TX: J1.3, Q7.6 (D), R17.1, SJ1.2
UART6_RX: Q7.4 (S), R18.1, SJ2.1, U1.P1$9 (PA12)
UART6_TX: Q7.1 (S), R19.1, SJ1.1, U1.P1$8 (PA11)

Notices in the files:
parts and their libraries:
SparkFun-Connectors: Licensing: Creative Commons ShareAlike 4.0 International - https://creativecommons.org/licenses/by-sa/4.0
microbuilder: This work is placed in the public domain, and may be freely used for commercial and non-commercial work with the following conditions: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
